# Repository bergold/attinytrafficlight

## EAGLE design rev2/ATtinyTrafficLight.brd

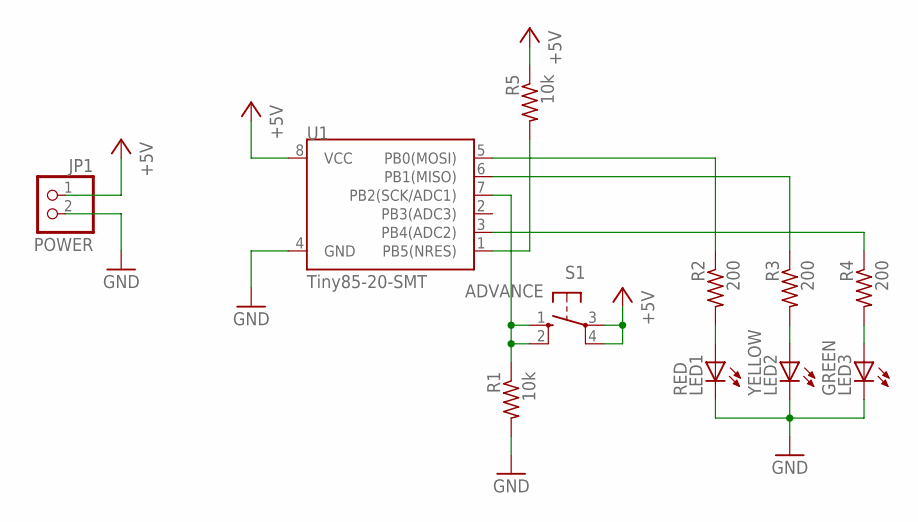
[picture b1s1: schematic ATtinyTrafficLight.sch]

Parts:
JP1: POWER; 1X02
LED1: RED; CHIPLED_0805
LED2: YELLOW; CHIPLED_0805
LED3: GREEN; CHIPLED_0805
R1, R5: 10k; R0805
R2, R3, R4: 200; R0805
S1: ADVANCE; B3F-10XX
U1: Tiny85-20-SMT; SO08-EIAJ

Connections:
+5V: JP1.1, R5.1, S1.3, S1.4 (P1), U1.8 (VCC)
GND: JP1.2, LED1.C, LED2.C, LED3.C, R1.2, U1.4 (GND)
unnamed: R5.2, U1.1 (PB5(NRES))
unnamed: R2.1, U1.5 (PB0(MOSI))
unnamed: R3.1, U1.6 (PB1(MISO))
unnamed: R1.1, S1.1 (S), S1.2 (S1), U1.7 (PB2(SCK/ADC1))
unnamed: R4.1, U1.3 (PB4(ADC2))
unnamed: LED1.A, R2.2
unnamed: LED2.A, R3.2
unnamed: LED3.A, R4.2

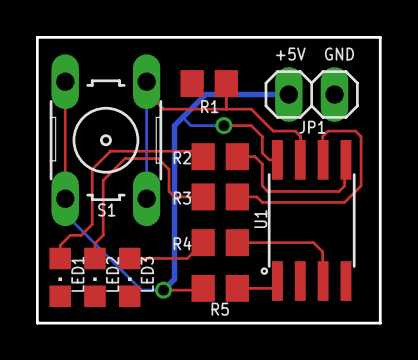
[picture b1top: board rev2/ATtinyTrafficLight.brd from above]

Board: 2 copper layers, 19.1 x 15.9 mm, 11 parts (0 on the bottom side), 10 nets.

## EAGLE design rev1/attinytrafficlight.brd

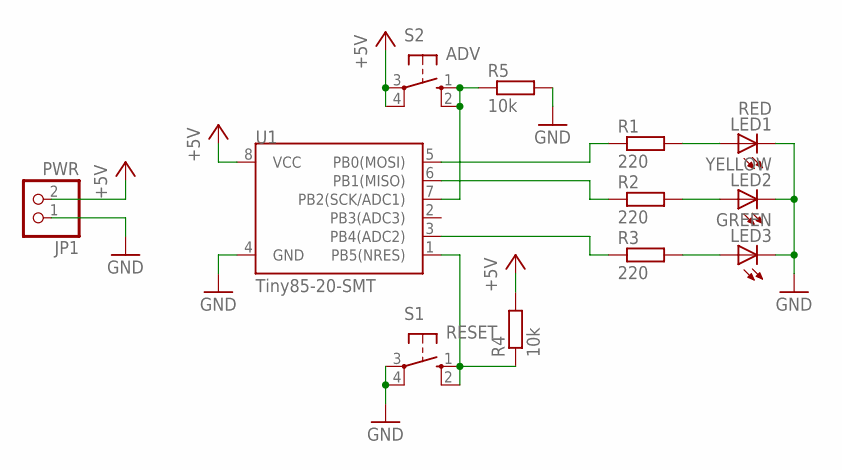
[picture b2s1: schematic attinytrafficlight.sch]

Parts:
JP1: PWR; 1X02
LED1: RED; SML0805
LED2: YELLOW; SML0805
LED3: GREEN; SML0805
R1, R2, R3: 220; R0805
R4, R5: 10k; R0805
S1: RESET; B3F-10XX
S2: ADV; B3F-10XX
U1: Tiny85-20-SMT; SO08-EIAJ

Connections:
+5V: JP1.2, R4.2, S2.3, S2.4 (P1), U1.8 (VCC)
GND: JP1.1, LED1.C, LED2.C, LED3.C, R5.2, S1.3, S1.4 (P1), U1.4 (GND)
unnamed: R4.1, S1.1 (S), S1.2 (S1), U1.1 (PB5(NRES))
unnamed: R5.1, S2.1 (S), S2.2 (S1), U1.7 (PB2(SCK/ADC1))
unnamed: R1.1, U1.5 (PB0(MOSI))
unnamed: R2.1, U1.6 (PB1(MISO))
unnamed: R3.1, U1.3 (PB4(ADC2))
unnamed: LED1.A, R1.2
unnamed: LED2.A, R2.2
unnamed: LED3.A, R3.2

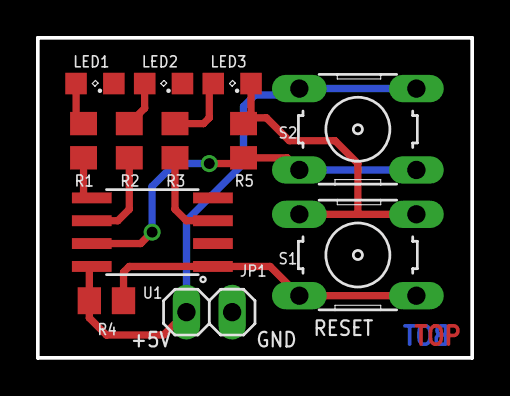
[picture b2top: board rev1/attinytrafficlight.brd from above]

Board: 2 copper layers, 24.1 x 17.8 mm, 12 parts (0 on the bottom side), 10 nets.

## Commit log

2016-02-25 :lollipop: Added .gitattributes & .gitignore files
2016-02-25 initial design
2016-02-25 add author and version on silk
2016-02-25 add top and bot markings in copper
2016-02-25 Schematic frame info
2016-03-05 add second rev

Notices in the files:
parts and their libraries:
SparkFun-DigitalIC: Licensing: Creative Commons ShareAlike 4.0 International - https://creativecommons.org/licenses/by-sa/4.0
